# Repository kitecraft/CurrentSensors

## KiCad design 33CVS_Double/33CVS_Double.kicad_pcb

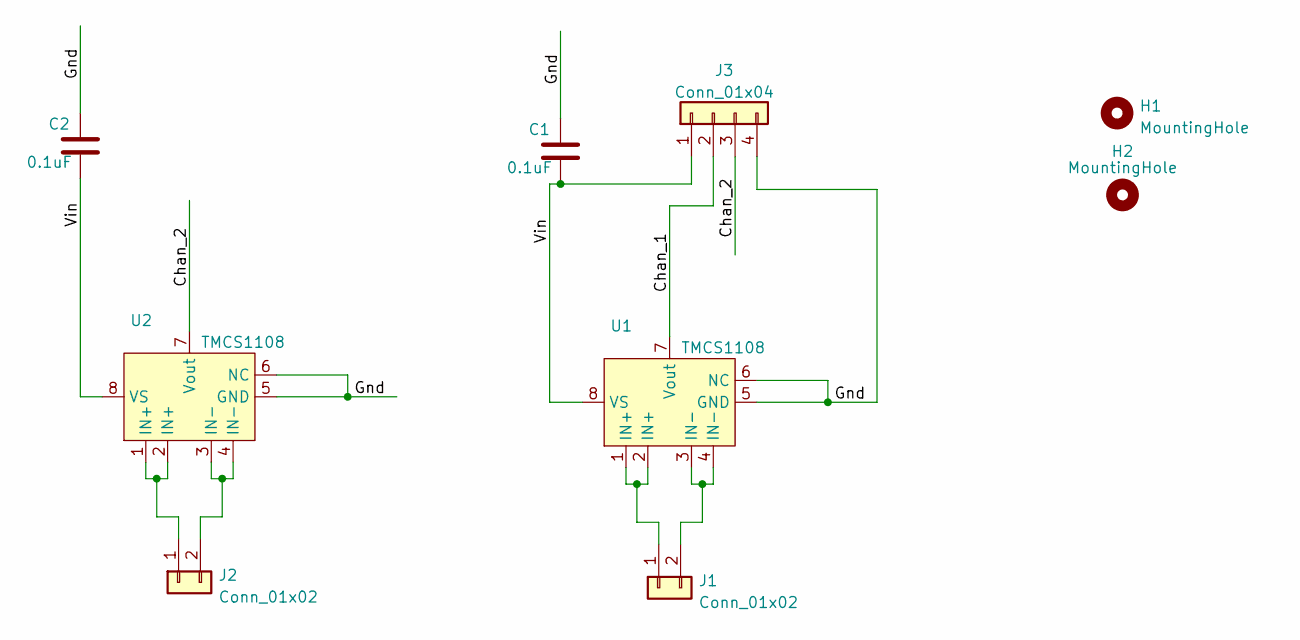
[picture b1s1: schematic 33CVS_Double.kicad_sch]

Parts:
C1, C2: 0.1uF; C_0805_2012Metric_Pad1.18x1.45mm_HandSolder
H1, H2: MountingHole; MountingHole_2.2mm_M2_DIN965
J1, J2: Conn_01x02; TerminalBlock_Phoenix_MKDS-1,5-2_1x02_P5.00mm_Horizontal
J3: Conn_01x04; PinHeader_1x04_P2.54mm_Vertical
U1, U2: TMCS1108; SO-8_3.9x4.9mm_P1.27mm

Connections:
/Chan_1: J3.2, U1.7 (Vout)
/Chan_2: J3.3, U2.7 (Vout)
/Gnd: C1.2, C2.2, J3.4, U1.5 (GND), U1.6 (NC), U2.5 (GND), U2.6 (NC)
/Vin: C1.1, C2.1, J3.1, U1.8 (VS), U2.8 (VS)
unnamed: J1.1, U1.1 (IN+), U1.2 (IN+)
unnamed: J1.2, U1.3 (IN-), U1.4 (IN-)
unnamed: J2.1, U2.1 (IN+), U2.2 (IN+)
unnamed: J2.2, U2.3 (IN-), U2.4 (IN-)

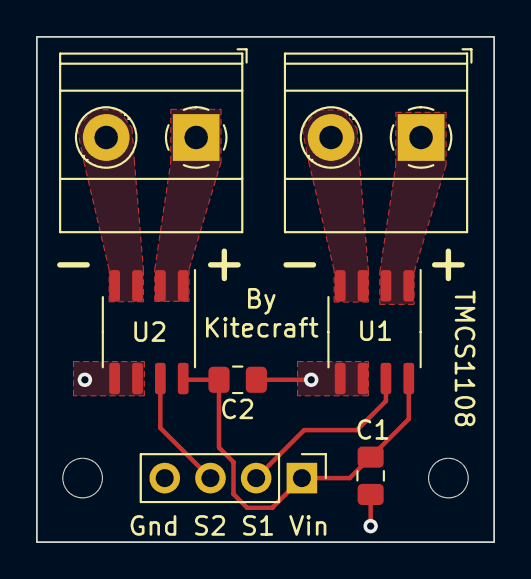
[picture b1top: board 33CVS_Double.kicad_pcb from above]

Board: 2 copper layers, 25.4 x 28.1 mm, 9 parts (0 on the bottom side), 8 nets.

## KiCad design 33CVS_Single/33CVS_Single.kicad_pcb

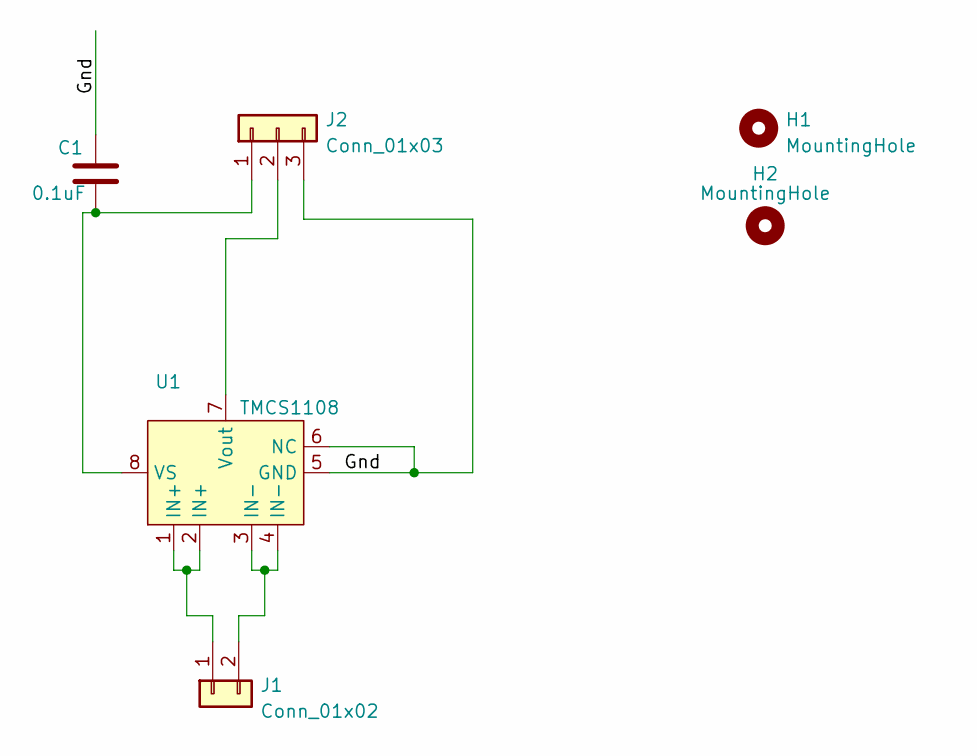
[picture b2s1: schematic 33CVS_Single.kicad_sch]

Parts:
C1: 0.1uF; C_0805_2012Metric_Pad1.18x1.45mm_HandSolder
H1, H2: MountingHole; MountingHole_2.2mm_M2_DIN965
J1: Conn_01x02; TerminalBlock_Phoenix_MKDS-1,5-2_1x02_P5.00mm_Horizontal
J2: Conn_01x03; PinHeader_1x03_P2.54mm_Vertical
U1: TMCS1108; SO-8_3.9x4.9mm_P1.27mm

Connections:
/Gnd: C1.2, J2.3, U1.5 (GND), U1.6 (NC)
unnamed: C1.1, J2.1, U1.8 (VS)
unnamed: J1.1, U1.1 (IN+), U1.2 (IN+)
unnamed: J1.2, U1.3 (IN-), U1.4 (IN-)
unnamed: J2.2, U1.7 (Vout)

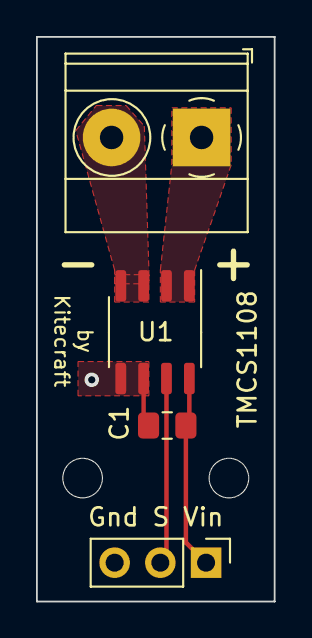
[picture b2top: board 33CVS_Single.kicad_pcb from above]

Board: 2 copper layers, 13.2 x 31.4 mm, 6 parts (0 on the bottom side), 5 nets.

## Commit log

2022-12-18 Adding projects for breakout boards for TMCS1108 current sensor
